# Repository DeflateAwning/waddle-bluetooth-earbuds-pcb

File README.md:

# waddle-bluetooth-earbuds-pcb
A PCB to drive KZ-ATE or similar earbuds wirelessly, because all other cheap wireless earbuds suck.

After trying a variety of wireless earbuds (which go directly in your ear), I set out to combine the high quality of the wired KZ-ATE family of earbuds with the convenience of wireless earbuds (especially while wearing winter clothing).

## Core Components BOM
After creating the Requirements (below), the following rough BOM was picked out:

1. Bluetooth Module: [DFR0781 BT401 V3 module](https://www.dfrobot.com/product-2177.html), [Datasheet](https://wiki.dfrobot.com/Audio_BLE_SPP_Pass_Through_Module_Bluetooth_5.0_SKU_DFR0781)
2. Microcontroller: TBD
3. PCB: custom, designed in this repo with KiCAD
4. Battery: 3.7V nominal lipo battery, used in RC helicopters and similar. Uses a 2.54mm header pin as the connector.
5. Battery charge circuit: TBD
6. Earbuds: KZ-ATE (TBC), with wires cut

## Requirements
Prior to designing anything, laying out the requirements and a rough proposed solution is important.

### The Obvious
1. Be battery powered.
2. Optimize for low cost, small size, and good battery life.
3. Be wireless over bluetooth.
4. Sound good. No static.
5. Must have play/pause buttons, which are easily controllable. 

### Core Requirements
1. The PCB will contain a microcontroller, bluetooth module
2. The Bluetooth module must be configurable. It must support play/pause, name changes, and audio beep configuration.
3. The PCB must drive two separate earbuds (left and right).
4. The PCB must have a battery and charging circuit.
5. USB-C only.
6. LED indicator(s) for currently playing, powered on, state-of-charge.
7. Good volume control, with a range of options over the spectrum.
8. Under CAD$80 unit cost.
9. Easy-to-control gestures via capacitive touch or tactile buttons.
10. 5h battery life.
11. Easy integration with a 3D printed case by smart layout and/or mounting holes.

### Ideal Requirements
The following features will be considered, and will be integrated if possible:

1. Control by capacitive touch.
2. Have two separate identical PCBs, one for each ear. More than likely though, there will only be a single PCB, which sits behind the user's neck or dangles in front.
3. Serial debugging if you plug it into a cell phone.
4. Equilizer of some sort.
5. >10h battery life, and/or changable batteries.
6. Include a microphone, and/or make the mic possible to disable.
7. Potentially integrate a microSD card right on the board, if beneficial.

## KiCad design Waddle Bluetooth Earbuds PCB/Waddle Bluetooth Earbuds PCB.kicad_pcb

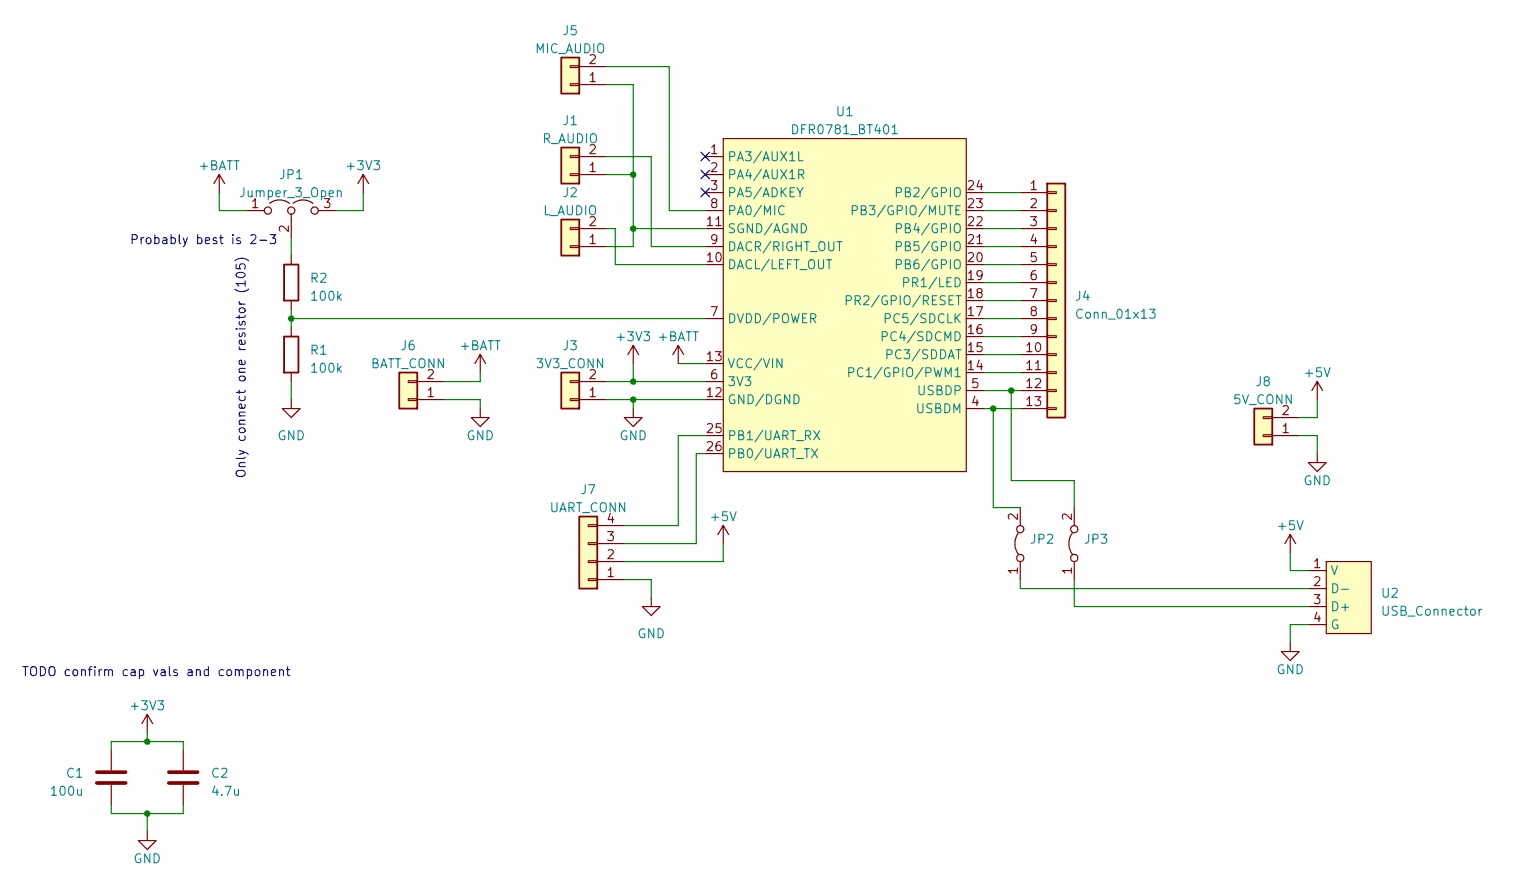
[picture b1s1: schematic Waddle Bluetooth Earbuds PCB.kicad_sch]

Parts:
C1: 100u; C_1206_3216Metric_Pad1.33x1.80mm_HandSolder
C2: 4.7u; C_1206_3216Metric_Pad1.33x1.80mm_HandSolder
J1: R_AUDIO; PinHeader_1x02_P1.27mm_Vertical
J2: L_AUDIO; PinHeader_1x02_P1.27mm_Vertical
J3: 3V3_CONN; PinHeader_1x02_P1.27mm_Vertical
J4: Conn_01x13; PinHeader_1x13_P1.27mm_Vertical
J5: MIC_AUDIO; PinHeader_1x02_P1.27mm_Vertical
J6: BATT_CONN; PinHeader_1x02_P1.27mm_Vertical
J7: UART_CONN; PinHeader_1x04_P1.27mm_Vertical
J8: 5V_CONN; PinHeader_1x02_P1.27mm_Vertical
JP1: Jumper_3_Open; SolderJumper-3_P1.3mm_Open_RoundedPad1.0x1.5mm_NumberLabels
JP2, JP3: Jumper_2_Bridged; SolderJumper-2_P1.3mm_Open_RoundedPad1.0x1.5mm
R1, R2: 100k; R_1206_3216Metric_Pad1.30x1.75mm_HandSolder
U1: DFR0781_BT401; DFR0781_BT401_V3
U2: USB_Connector

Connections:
+3V3: C1.1, C2.1, J3.2, JP1.3 (B), U1.6 (3V3)
+5V: J7.2, J8.2, U2.1 (V)
+BATT: J6.2, JP1.1 (A), U1.13 (VCC/VIN)
GND: C1.2, C2.2, J3.1, J6.1, J7.1, J8.1, R1.2, U1.12 (GND/DGND), U2.4 (G)
unnamed: J1.1, J2.1, J5.1, U1.11 (SGND/AGND)
unnamed: J1.2, U1.9 (DACR/RIGHT_OUT)
unnamed: J2.2, U1.10 (DACL/LEFT_OUT)
unnamed: J4.1, U1.24 (PB2/GPIO)
unnamed: J4.2, U1.23 (PB3/GPIO/MUTE)
unnamed: J4.3, U1.22 (PB4/GPIO)
unnamed: J4.4, U1.21 (PB5/GPIO)
unnamed: J4.5, U1.20 (PB6/GPIO)
unnamed: J4.6, U1.19 (PR1/LED)
unnamed: J4.7, U1.18 (PR2/GPIO/RESET)
unnamed: J4.8, U1.17 (PC5/SDCLK)
unnamed: J4.9, U1.16 (PC4/SDCMD)
unnamed: J4.10, U1.15 (PC3/SDDAT)
unnamed: J4.11, U1.14 (PC1/GPIO/PWM1)
unnamed: J4.12, JP3.2 (B), U1.5 (USBDP)
unnamed: J4.13, JP2.2 (B), U1.4 (USBDM)
unnamed: J5.2, U1.8 (PA0/MIC)
unnamed: J7.3, U1.26 (PB0/UART_TX)
unnamed: J7.4, U1.25 (PB1/UART_RX)
unnamed: JP1.2 (C), R2.1
unnamed: JP2.1 (A), U2.2 (D-)
unnamed: JP3.1 (A), U2.3 (D+)
unnamed: R1.1, R2.2, U1.7 (DVDD/POWER)

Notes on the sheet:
TODO confirm cap vals and component
Only connect one resistor (105)
Probably best is 2-3

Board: 2 copper layers, 16 parts (0 on the bottom side), 25 nets, no tracks yet.

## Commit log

2023-05-18 Add intro README
2023-05-18 Add BT module symbol
2023-05-22 Add core bluetooth circuits
